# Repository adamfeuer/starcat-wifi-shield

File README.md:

Wifi Shield for Arduino Due
===========================

This is a wifi shield for Arduino Due, providing a connector to mount an
[Arietta SAM9G Linux module](http://www.acmesystems.it/arietta).

The purpose of this shield is to connect the Arduino Due to the Internet
via a USB connection to Linux running on the wifi-enabled Arietta board.

Eventually I would like to get OpenWRT running on the Arietta board instead of Debian,
so users can run a software stack similar to the [Arduino Yún](http://arduino.cc/en/Main/ArduinoBoardYun?from=Products.ArduinoYUN).

* [Arietta shield schematic](https://github.com/adamfeuer/arietta-shield/blob/master/arietta-shield.pdf)
* [Arietta shield PCB layout](https://github.com/adamfeuer/arietta-shield/blob/master/arietta-shield.png)
* [Arietta shield gerber files](https://github.com/adamfeuer/arietta-shield/blob/master/cam/arietta-shield-oshpark-files-2014-12-01-1848.zip?raw=true) - suitable for submitting to [OSH Park](https://oshpark.com/).

If there's enough interest, I may decide to manufacture this board;
if you'd like to be notified if that happens, [you can sign up here](http://starcat.io/arietta-shield/).

Until then, you can make your own. Unfortunately, I can't provide support for it.
Good luck!

Features
========

* USB type A female connector that powers the Arietta module.
* A short male micro-B to male type A USB cable connects the wifi shield to the Arduino Due.
 * [5 inch male micro-B to male A cable](http://www.amazon.com/gp/product/B00JX1260Y/) - this is inexpensive and works well
 * Provides USB 2.0 480Mbps connection to the Arduino Due using equal-length differential traces.

Notes
=====

* The schematic and PCB layout were done in [Eagle CAD 6.5](http://www.cadsoftusa.com/).
* The PCB is a 2-layer board.
* This the the USB connector used - [TE Connectivity USB A Female](http://www.digikey.com/product-search/en?KeyWords=A31726-ND&WT.z_header=search_go) - manufacturer part number 292303-1
* Arduino shield connectors are from [4UCon](http://www.4uconnector.com/), ordered from eBay sellers.

License
=======

[Creative Commons By-Attribution ShareAlike 4.0](https://creativecommons.org/licenses/by-sa/4.0/)

Comments
========

If you have questions, comments, or improvements, I would love to know them!

cheers <br>
adam <br>
Adam Feuer <br>
Seattle, WA, USA <br>
adam@adamfeuer.com <br>
http://adamfeuer.com <br>

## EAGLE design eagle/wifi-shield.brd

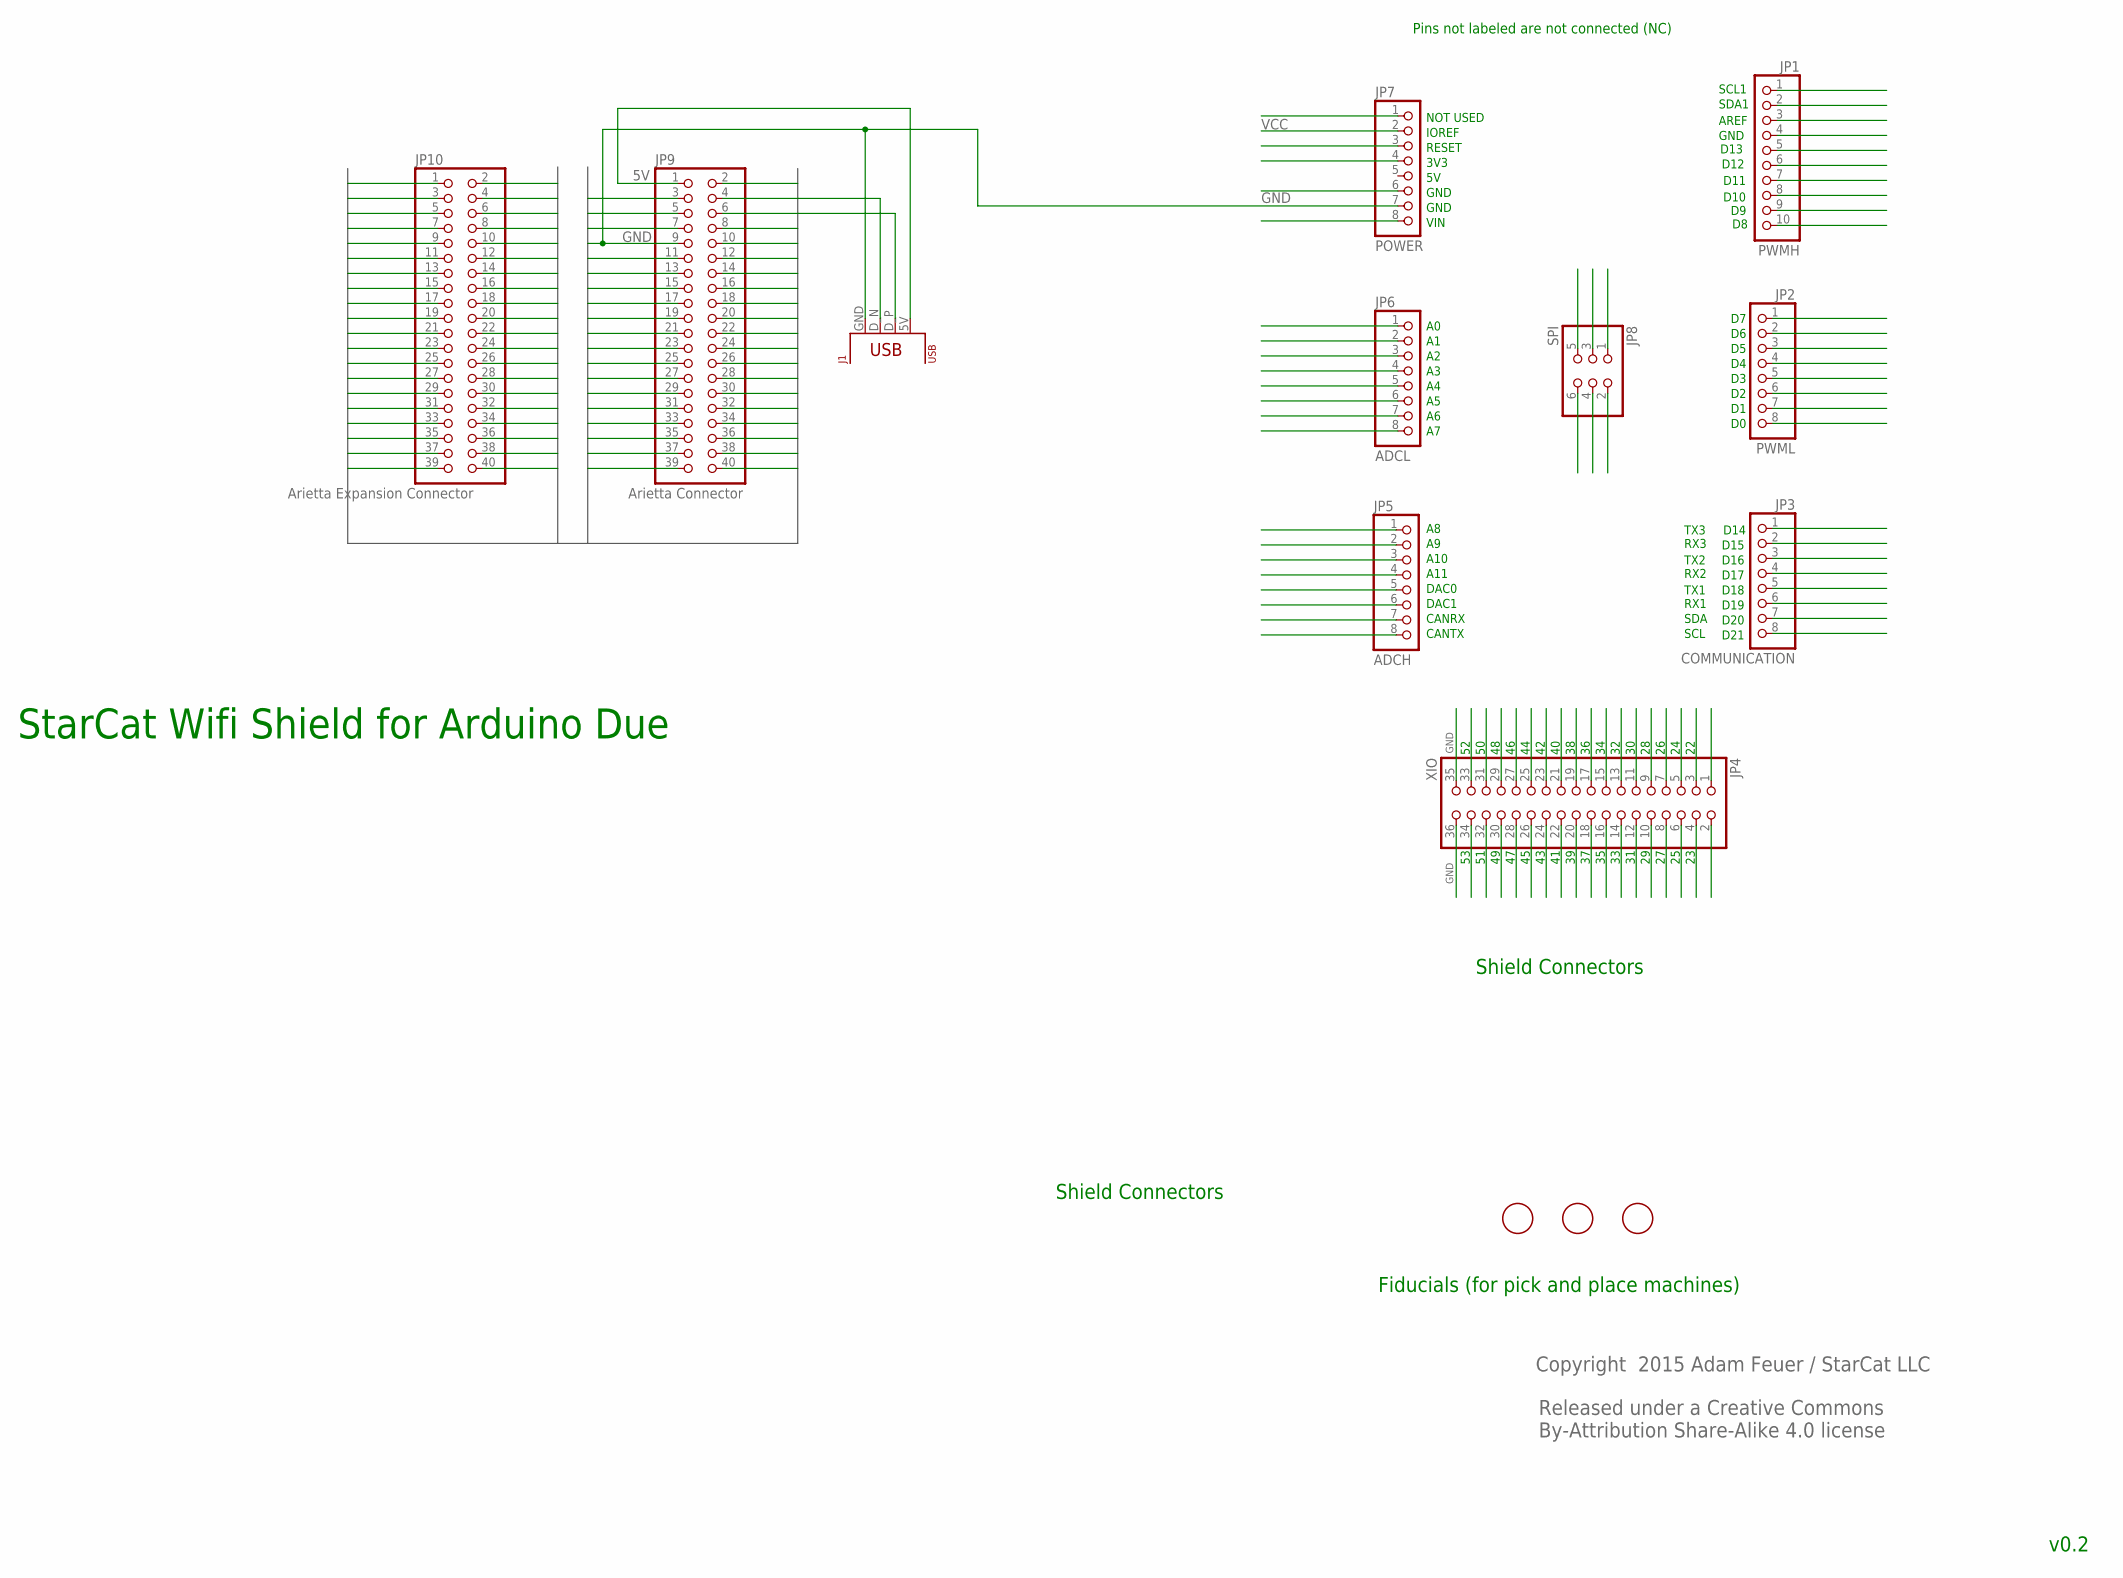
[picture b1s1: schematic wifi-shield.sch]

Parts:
J1: USB; USB-A-FEMALE-RIGHT-ANGLE
JP1: PWMH; 1X10
JP2: PWML; 1X08
JP3: COMMUNICATION; 1X08
JP4: XIO; 2X18
JP5: ADCH; 1X08
JP6: ADCL; 1X08
JP7: POWER; 1X08
JP8: SPI; 2X03
JP9: Arietta Connector; 2X20
JP10: Arietta Expansion Connector; 2X20
U$2, U$5, U$6: FIDUCIAL; FIDUCIAL_1MM

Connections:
5V: J1.5V, JP9.1, JP10.1
D2: JP9.2, JP10.2
D3: JP9.3, JP10.3
D5: JP9.5, JP10.5
D7: JP9.7, JP10.7
D8: JP9.8, JP10.8
D10: JP9.10, JP10.10
D11: JP9.11, JP10.11
D12: JP9.12, JP10.12
D13: JP9.13, JP10.13
D14: JP9.14, JP10.14
D15: JP9.15, JP10.15
D16: JP9.16, JP10.16
D17: JP9.17, JP10.17
D18: JP9.18, JP10.18
D19: JP9.19, JP10.19
D20: JP9.20, JP10.20
D21: JP9.21, JP10.21
D22: JP9.22, JP10.22
D23: JP9.23, JP10.23
D24: JP9.24, JP10.24
D25: JP9.25, JP10.25
D26: JP9.26, JP10.26
D27: JP9.27, JP10.27
D28: JP9.28, JP10.28
D29: JP9.29, JP10.29
D30: JP9.30, JP10.30
D31: JP9.31, JP10.31
D32: JP9.32, JP10.32
D33: JP9.33, JP10.33
D34: JP9.34, JP10.34
D35: JP9.35, JP10.35
D36: JP9.36, JP10.36
D37: JP9.37, JP10.37
D38: JP9.38, JP10.38
D39: JP9.39, JP10.39
D40: JP9.40, JP10.40
D43: JP4.24
D45: JP4.26
D_N: J1.D_N, JP9.4, JP10.4
D_P: J1.D_P, JP9.6, JP10.6
GND: J1.GND, JP4.35, JP4.36, JP7.7, JP9.9, JP10.9
GND1: JP8.6
RESET: JP8.5
SPI0_MISO: JP8.1
SPI0_MOSI: JP8.4
SPI0_SCK: JP8.3
VCC: JP7.2
VCC_5V: JP8.2

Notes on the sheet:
Released under a Creative Commons By-Attribution Share-Alike 4.0 license
Copyright 2015 Adam Feuer / StarCat LLC
Shield Connectors
A10
A11
DAC0
DAC1
CANRX
CANTX
NOT USED
IOREF
RESET
3V3
GND
VIN
Fiducials (for pick and place machines)
Pins not labeled are not connected (NC)
SCL1
SDA1
AREF
D13
D12
D11
D10
D14
D15
D16
D17
D18
D19
D20
D21
TX2
RX2
TX3
RX3
TX1
RX1
SDA
SCL

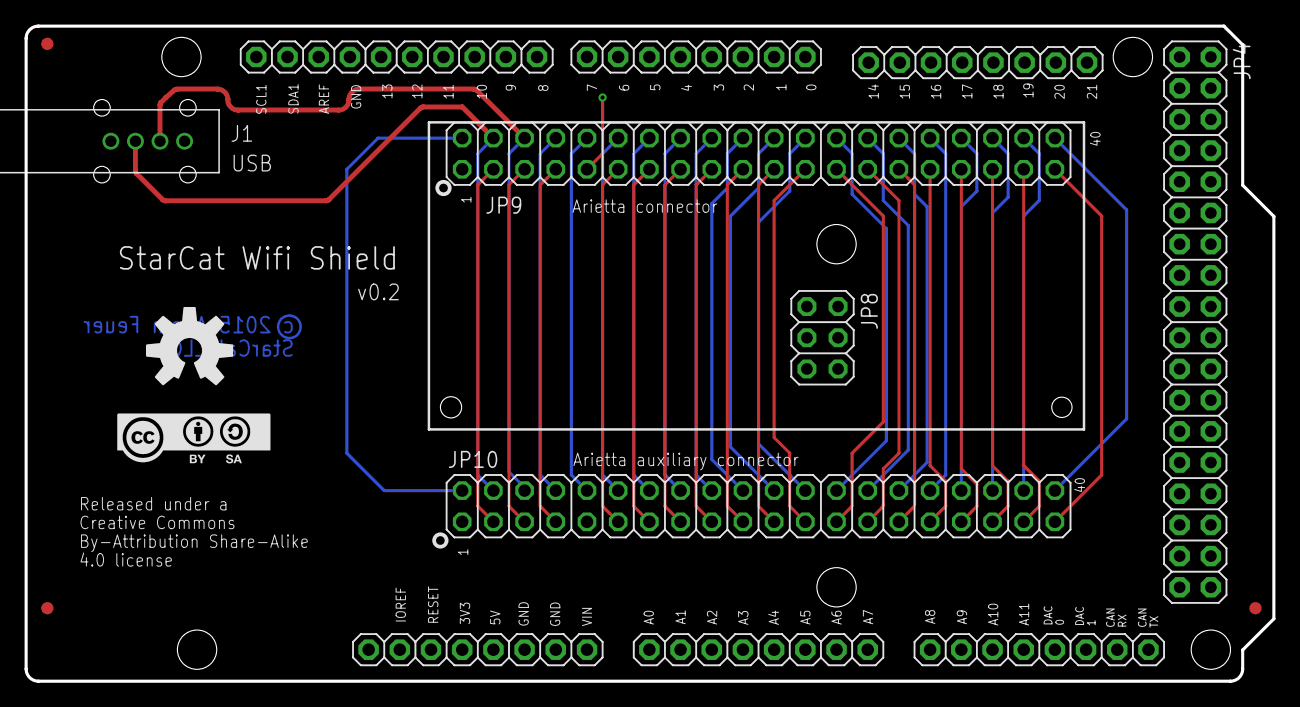
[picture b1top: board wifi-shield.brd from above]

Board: 2 copper layers, 101.6 x 53.3 mm, 16 parts (0 on the bottom side), 40 nets.

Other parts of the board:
U$1: OSHW-LOGO-L
U$8: CC-BY-SA

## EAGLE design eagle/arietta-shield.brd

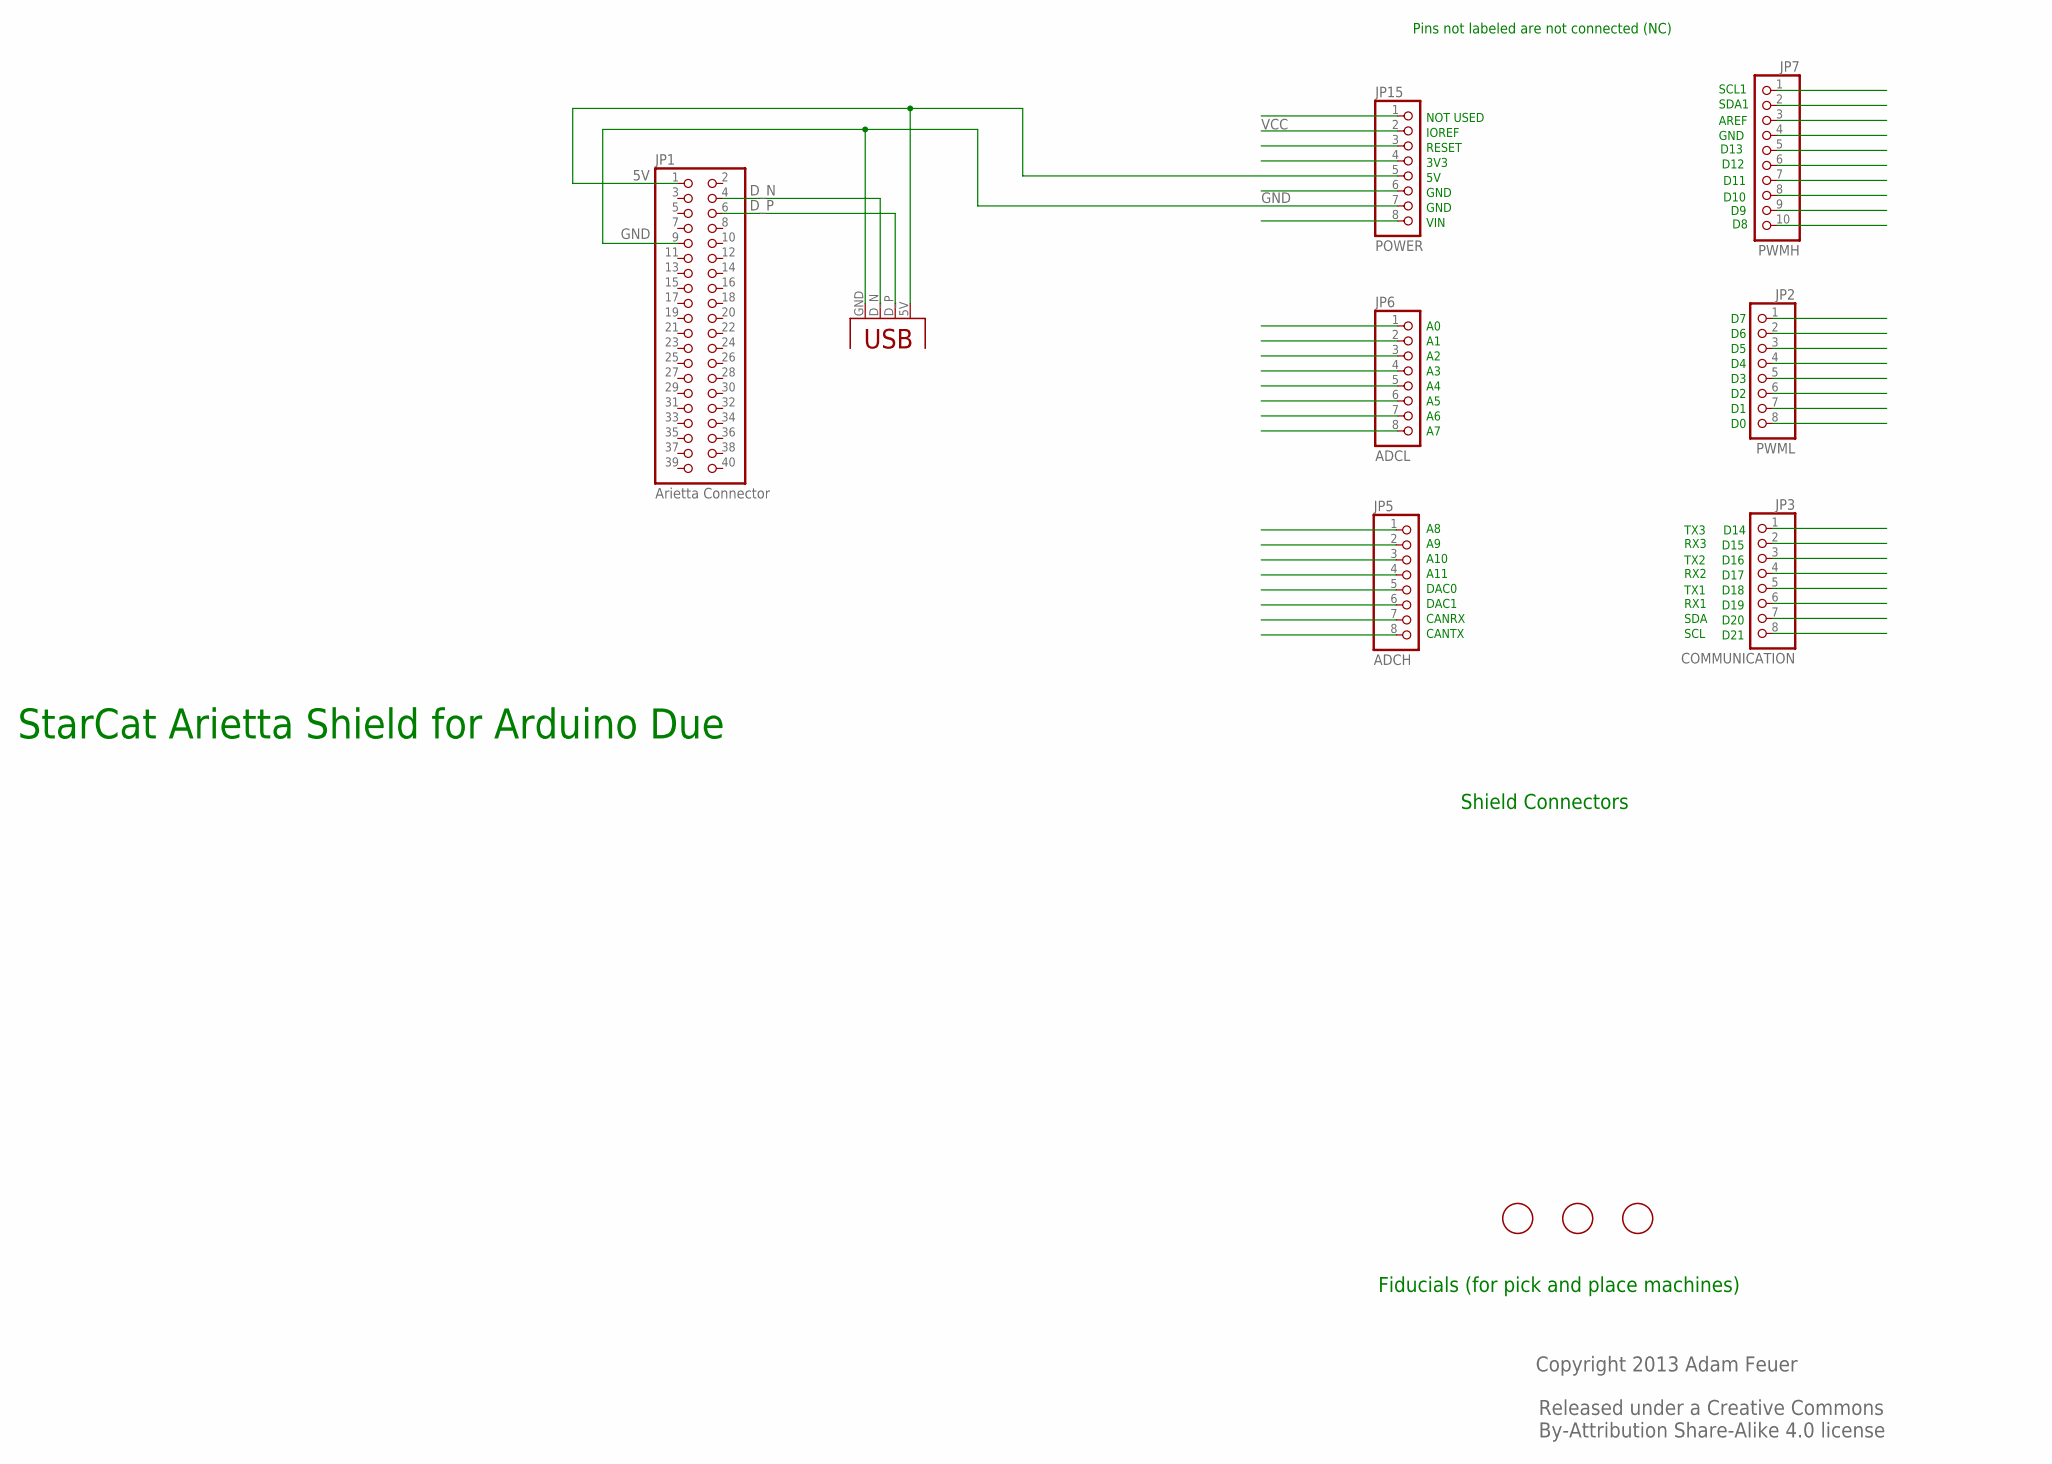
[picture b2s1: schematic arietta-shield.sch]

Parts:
JP1: Arietta Connector; 2X20
JP2: PWML; 1X08
JP3: COMMUNICATION; 1X08
JP5: ADCH; 1X08
JP6: ADCL; 1X08
JP7: PWMH; 1X10
JP15: POWER; 1X08
U$2, U$5, U$6: FIDUCIAL; FIDUCIAL_1MM
U$7: USB-A-FEMALE

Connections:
5V: JP1.1, JP15.5, U$7.5V
D_N: JP1.4, U$7.D_N
D_P: JP1.6, U$7.D_P
GND: JP1.9, JP15.7, U$7.GND
VCC: JP15.2

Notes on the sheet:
Released under a Creative Commons By-Attribution Share-Alike 4.0 license
Copyright 2013 Adam Feuer
Shield Connectors
A10
A11
DAC0
DAC1
CANRX
CANTX
NOT USED
IOREF
RESET
3V3
GND
VIN
Fiducials (for pick and place machines)
Pins not labeled are not connected (NC)
SCL1
SDA1
AREF
D13
D12
D11
D10
D14
D15
D16
D17
D18
D19
D20
D21
TX2
RX2
TX3
RX3
TX1
RX1
SDA
SCL

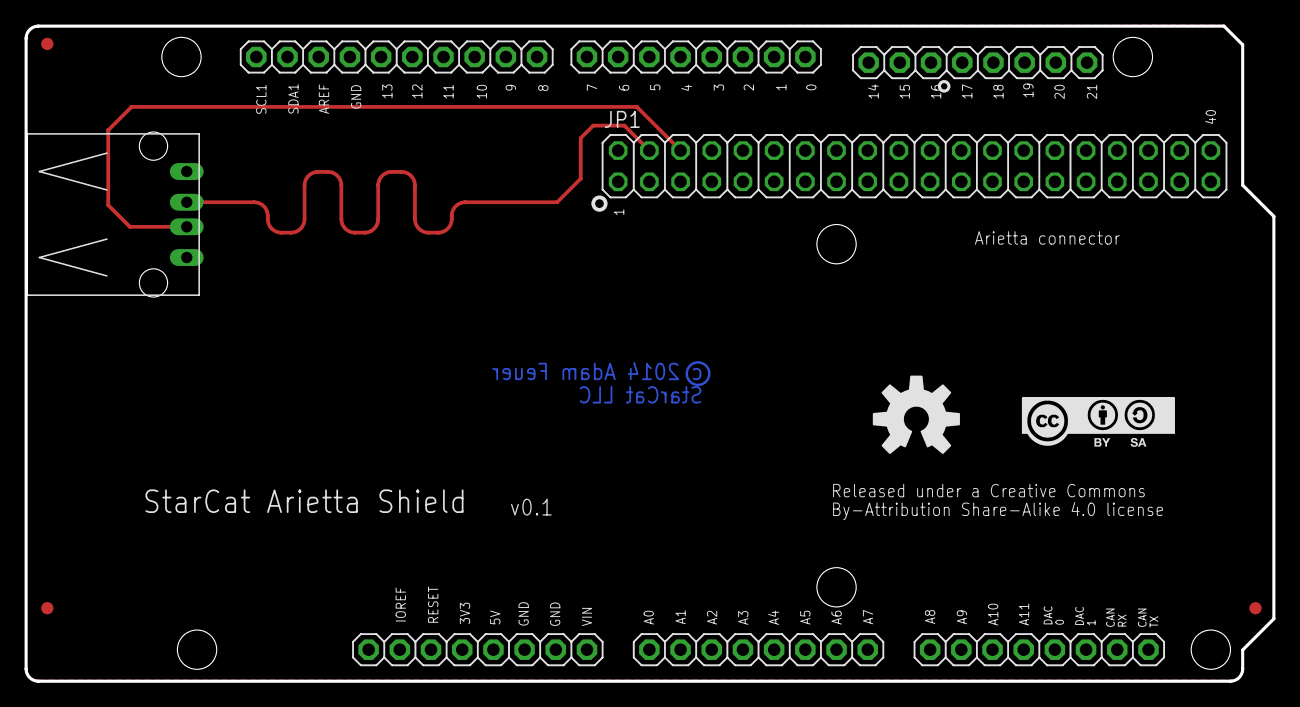
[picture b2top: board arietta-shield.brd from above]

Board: 2 copper layers, 101.6 x 53.3 mm, 13 parts (0 on the bottom side), 4 nets.

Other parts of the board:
U$1: OSHW-LOGO-L
U$8: CC-BY-SA

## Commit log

2014-12-02 Adding LICENSE and README.md file
2014-12-02 added unpopulated SPI and rear connectors
    - 5V now only connected to USB now, not shield connector,
    enabling connection to another computer when connected to
    the Arduino Due
2014-12-02 minor updates to wording of README
2014-12-02 adding schematic PDF and board PNG
2014-12-02 added board schematic and PCB PNG to README
2014-12-02 wording change - removed Debian from purpose description
2014-12-02 clarified USB differential traces in README
2014-12-02 adding gerber files suitable for OSH Park
2014-12-02 adding arietta cam job
2014-12-02 adding OSH Park DRU file
2014-12-02 adding gerber files package to README
2014-12-02 README wording change
2014-12-02 added notes to README
2014-12-02 linked to starcat.io webpage
2014-12-03 added stackup.txt
2014-12-03 simplified email signup wording
2014-12-04 renamed arietta shield to wifi shield
    - due to potential trademark issues
2014-12-05 wording changes to README
2014-12-05 updated PCB picture with board name change
2015-01-02 moved BOM to separate repo
2015-01-02 added flag-style vertical right angle USB package
2015-01-02 added Arietta expansion connector
    - to schematic, but not routed yet
2015-01-02 added necessary cam files
    - copied from hackeeg shield
2015-01-02 corrected and routed Arietta auxiliary connector
    - net classes are correct
    - ERC and DRC pass
2015-01-02 updated board picture

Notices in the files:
parts and their libraries:
SparkFun-Aesthetics: Licensing: CC v3.0 Share-Alike You are welcome to use this library for commercial purposes.
